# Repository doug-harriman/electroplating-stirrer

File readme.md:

View this project on [CADLAB.io](https://cadlab.io/project/27601).

# Firmware

## Compiler

`sudo apt install make gcc-avr avr-libc avrdude`

## Programmer

* [Amazon](https://www.amazon.com/gp/product/B09X1W2TPG/)
* [SparkFun Docs](https://www.sparkfun.com/products/11801)

### WSL USB

**Note** [Simplexity documentation](https://simplexity.atlassian.net/wiki/spaces/FWSW/pages/2658566527/Docker#Host-Access) on forwarding USB to a Docker container in WSL.

Overview of [WSL USB access](https://learn.microsoft.com/en-us/windows/wsl/connect-usb).

1. Install the WSL drivers for your kernel.
    1. Open a WSL terminal and run `usbipd list`.  This will display packages that need to be installed for your WSL kernel.
    1. Install those packages.

1. Install the [programmer Windows driver](https://github.com/adafruit/Adafruit_Windows_Drivers/releases) & plug in the programmer.
   * Windows device manager should now show `libusb-win32 devices -> USBtiny`

1. Make the USB device available to WSL
    1. Open a WSL shell.
    1. List available USB devices: `usbipd.exe list`.  Find the `USBtiny` device and note the bus ID.
        * Note: This is calling a Windows executable from WSL.
    1. Attach the USB device to WSL: `usbipd.exe wsl attach --busid <bus ID>`.  The device should now be available in WSL.
        * When you're done with the device, detach with the command above, substituting `detach` for `attach`.
    1. Verify the device is available in an WSL terminal: `lsusb`.  The device should be listed.

1. Create a `udev` rules file to make the device accessible to `avrdude`.
    1. After attaching the device to WSL per above, run `lsusb` to get the `idVendor` and `idProduct` values needed next.  The output should look something like this:
        ```
        Bus 001 Device 002: ID 1781:0c9f Multiple Vendors USBtiny
        ```
        In this example (default for the usbtiny programmer), the `idVendor` is `1781` and the `idProduct` is `0c9f`.

    1. Create a file `/etc/udev/rules.d/99-usb.rules` with the following contents:
        ```
        SUBSYSTEM=="usb", ATTR{idVendor}=="1781", ATTR{idProduct}=="0c9f", MODE="0660", GROUP="plugdev"
        ```
        * The `idVendor` and `idProduct` values are from the output of `usbipd list` above.
    1. Add your user to the group.  This will require logging out and back in.
        ```
        sudo usermod -a -G plugdev $USER
        ```
    1. Reload the `udev` rules: `sudo udevadm control --reload-rules && sudo udevadm trigger`

    NOTE: If you're unable to access, try with `sudo` permissions.

https://devblogs.microsoft.com/commandline/connecting-usb-devices-to-wsl/

https://www.krekr.nl/content/using-usbtinyisp-with-ubuntu/
https://www.tonymitchell.ca/posts/programming-avr-in-wsl-tips-and-tricks/

## Simulator

[SimAVR](https://github.com/buserror/simavr)

`sudo apt install simavr`

also installs `gdb-avr` as a dependency.

To run a simulation, you need a special build that brings in simulator symbols.
See `main-sim.c`

`make sim`

If you run the simulator with the `-g` flag, it will open up a gdb server port.
You can then attach a GDB session to that port.

## Debugger

* VSCode launch target defined in `.vscode/launch.json`
* `make sim-debug` to build the debug target and lanch the gdb-avr server process.
    * Needs to be redone every code change.
    * Make sure to kill the debugger if you relaunch.
* Select the VSCode debug and run with the AVR Debug configuration.

# Electronics

## AtTiny85

[Amazon](https://www.amazon.com/gp/product/B0CHQ97KQZ/)
* \$13.29 for 5 pieces = $2.66/piece, though had free deliverey.
* Digikey has for \$1.66/piece in quantity 1, $1.52 in quantity 25.

## Servo Motor

[Amazon](https://www.amazon.com/gp/product/B092VN3MTX/)

## Poteniometer

[Amazon](https://www.amazon.com/gp/product/B09897HR3C/)

  You may need to install the following packages for this specific kernel:
    linux-tools-5.15.90.1-microsoft-standard-WSL2
    linux-cloud-tools-5.15.90.1-microsoft-standard-WSL2

  You may also want to install one of the following packages to keep up to date:
    linux-tools-standard-WSL2
    linux-cloud-tools-standard-WSL2

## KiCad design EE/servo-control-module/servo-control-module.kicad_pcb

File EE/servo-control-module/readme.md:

# Workflow

> **Note**: For all operations, keep grbl software running and maintain XY home position.

> **Note**: [CADLAB.io](https://cadlab.io/project/27601/main/files) view of github repo.  Login with google account.

## PCB Prep

1. Clean the PCB with metal polisher to remove oxidation.  I use [Brasso](https://www.amazon.com/gp/product/B0000DCZ2X/).  PCB should be shiny and clean.
1. Spray paint the PCB.  Ideally would use solder mask, but the epoxy material is hard to fully ablate.  Paint ablates nicely, though it is prone to scratching.

## Design Prep
1. Panelize PCB using KiKit.  Use to provide frame and tabs with mousebites.  The `kikit.sh` script performs the process.
1. Load the panelized PCB into KiCAD.
1. Export a PCB image for laser ablation of the paint to expose the trace isolation areas.  Use the KiCAD "plot" function.  The image below shows the settings, assuming we're exposing the back side copper. 

## PCB Fabrication

1. Tape down PCB on mill.  Rough cut the PCB to size if that makes sense.
1. Expect to route/drill through the PCB into the supporting material, so use a sacrificial material.
1. Drill all holes, including tooling holes.
    * It is recommended
1. Route out panel from larger PCB.  Limit size of PCB we're working with to maintain chem etch solution.
1. Laser ablate spray paint in the PCB trace inverse to expose the copper for etching.
1. Chem etch the PCB to isolate the traces.
1. Laser ablate the spray paint on the solder pads.

### PCB Milling Operations

* Milling operations are generated using `pcb2gcode`.  This is a command line program that reads information from configuration files.
* `pcb2gcode` is called multiple times with different configuration files to generate the different G-code jobs (with different tools) required to machine out the PCB.

## KiCAD

KiCAD Gerber export: disable the "Use extended X2 format" option.

## PCB2GCODE

> Alternate software: https://sourceforge.net/p/pygerber2gcode/code/ci/master/tree/

* This tool worked great for generating G-code.
    * Much easier to use than FlatCAM.
    * Man page in file `pcb2gcode.pdf`.
* Example config file: `millproject`
* Generate code by running `pcb2gcode` in the same directory with `millproject`.
* Use a short list of drill sizes, or it will use exact drill size for each part.  That can lead to a lot of tooling changes.
* You can get some parameter by editing and running `pcb_calcs.py`.
    * The copper layer is very thin.  Got nice isolation with a margin of 0.5, could probably go lower.
    * This calcs the Z depth for drilling and edge cuts to cut into the tape.  It can be a bit tricky if you don't apply the height map.  Not clear if you can apply the height map to multiple files.
* Bridges shouldn't be necessary if you don't cut too fast on the edge cuts.
* Example call: https://gist.github.com/bullestock/87ed51aaadaae8b8d2f085756652eb04

## Soldermask & Silkscreen

Intended process is to apply two layers of soldermask/ink to the PCB, then use my UV laser to ablate the areas that I don't want filled in.  Overall technique from: https://www.youtube.com/watch?v=NuJlgw7E7vg.

Soldermask & silkscreen cating goes down nicely with silkscreen netting & squeegee.

* Use a squeegee to spread the ink.  I used Silicone squeegee from [Amazon](https://www.amazon.com/gp/product/B091KQFQVG/).
* Cure with UV light.  I use a resin printer cure station for 3 min with board leaning against lamp.

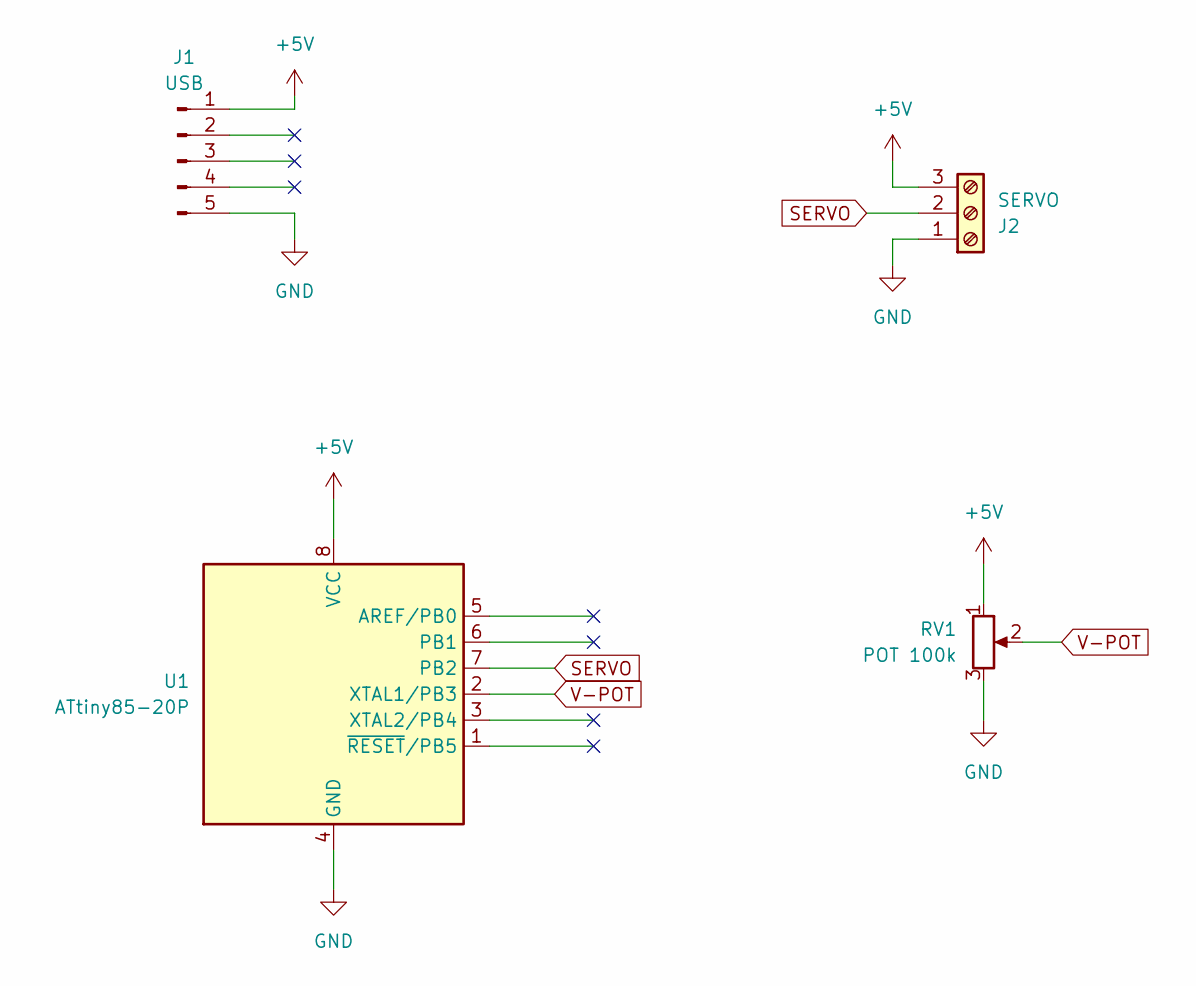
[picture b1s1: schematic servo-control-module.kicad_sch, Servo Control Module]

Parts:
J1: USB; USB-micro-breakout
J2: SERVO; TerminalBlock_TE_282834-3_1x03_P2.54mm_Horizontal
RV1: POT 100k; Potentiometer_Amazon_Single_Horizontal
U1: ATtiny85-20P; DIP-8_W7.62mm

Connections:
+5V: J1.1, J2.3, RV1.1, U1.8 (VCC)
GND: J1.5, J2.1, RV1.3, U1.4 (GND)
SERVO: J2.2, U1.7 (PB2)
V-POT: RV1.2, U1.2 (XTAL1/PB3)

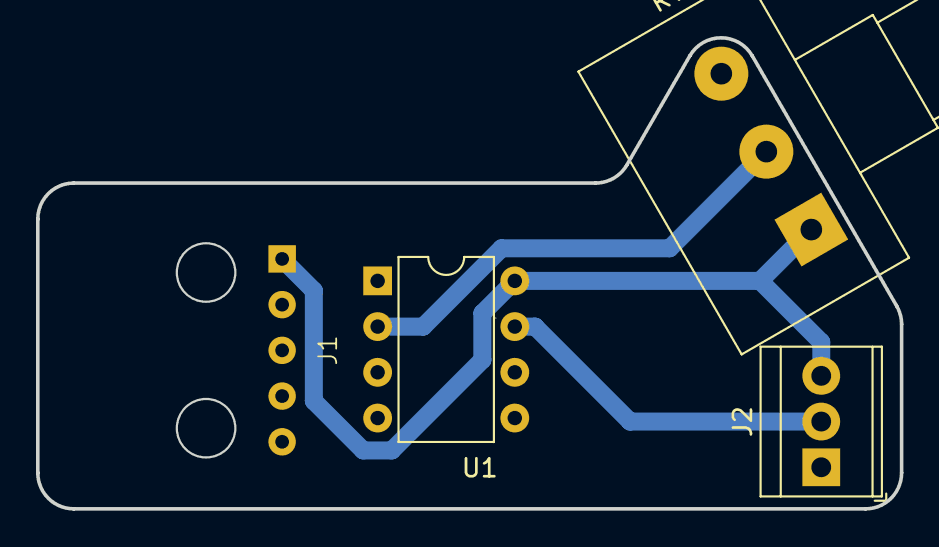
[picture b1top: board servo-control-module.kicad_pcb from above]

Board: 2 copper layers, 48.0 x 26.2 mm, 4 parts (0 on the bottom side), 4 nets.

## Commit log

2023-11-06 Initial commit due to git corruption.
2023-12-12 Backlink to CADLAB.io has been added.
2023-12-12 Updates for first milled board.
2023-12-17 Min 0.5 mm trace spacing for milling
2023-12-17 Doc & minor update to output.
2023-12-17 FW updates for ADC pin move reqd by layout.
    Using netlist.py to generate some of the code.
2023-12-17 Documentation capture
2023-12-17 Git ignore updates
2023-12-17 FlatCAM project add.
2023-12-17 Git ignore update.
2023-12-21 Added footprint and 3D model for USB breakout adapter.
2023-12-24 ME design first pass.
2024-01-16 Added PCB mill CAM files & info.
2024-01-16 Ignore CNC files for PCB.
2024-01-21 Update readme.md
    Added notes on soldermask & silkscreen.
2024-01-21 Update readme.md
    Added overall process steps list.
2024-01-21 Python generation of G-code for silksreen from Gerber
2024-01-22 Found another method to generate G-code
2024-01-22 Updated to-do's.
2024-01-22 Generating G-Code from Gerber geometry description.
2024-01-22 Git ignore update
2024-01-26 Rectangle GCode updated for different G-code geneation paradigm. Working for Gerber rectangular pad generation.
2024-01-26 Now able to rotate rectangular pads.
2024-01-26 Circle g-code generation working.
2024-01-27 Rectangle fill working
2024-01-27 Circle diameter line file.
2024-01-27 Circle fill working
2024-01-27 First pass 2D optimized scheduling working.
2024-01-27 Infill scheduling optimized.
2024-01-27 Shape startpoint optimization.
2024-01-27 Traveling salesman layout optimization working.
2024-01-28 Gerber Line object supported.
2024-01-28 Silkscreen G-CODE gen working.
2024-02-18 Soldermask clearing basically working.
2024-03-03 Updated to KiCad v8
2024-03-03 New Python module to generate fab files from KiCad files via kicad-cli.
2024-06-30 Added tasks.py
2024-10-29 Captured new files
2024-10-29 Added link to Simplexity documentation
2025-03-03 Remove solidworks files
2025-03-03 Remove STL's
2025-03-03 Added chassis parts, FreeCAD
2025-04-20 PCB fab documentation updates.
2025-04-20 Capture of initial KiKit info.
2025-04-27 Removing unneeded files
2025-04-27 Moved readme up a leve.
2025-04-27 M-CAD & E-CAD updates
2025-04-27 uv venv files added.
2025-04-27 Removed more unneeded files.
2025-04-27 Readme updates.
2025-04-27 Removed EE/CAM/tasks.py
2025-04-27 gitignore updates
2025-04-27 KiCAD CLI runner updates for latest Python.
2025-04-27 Automated workflow first partial pass capture.
2025-04-27 Changed import to allow clean to work in old Python
2025-04-27 Drill CNC file generated.
2025-04-27 Removed kikit docker runner
2025-04-27 PCB workflow task updates:
    * Abstracted all board filename checks.
    * added 'drills' to return PCB specified drill sizes.
    * pcb2gcode stdout dumped to /dev/null
2025-04-27 inv process now drills panel, not source pcb
2025-04-27 Python debugger launch file.
2025-04-27 Drill file split by drill size.
2025-04-27 Added edge cut gerber generation.
2025-04-27 Added edge cutting to process.
2025-04-27 Generate trace etch mask file
